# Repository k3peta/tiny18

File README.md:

# Tiny18

Tiny18 is a compact, 18-key wireless split keyboard designed for Japanese input. Each half uses a Seeed Studio XIAO nRF52840 and ZMK firmware.

日本語の説明は [`README.ja.md`](README.ja.md) を参照してください。

[Download the latest firmware](https://github.com/k3peta/zmk-config-tiny18/releases/latest) · [Firmware source](https://github.com/k3peta/zmk-config-tiny18) · [Keymap](https://github.com/k3peta/zmk-config-tiny18#default-keymap)

## Features

- 18 keys total (9 per half)
- Wireless split using Bluetooth Low Energy
- Seeed Studio XIAO nRF52840 controllers
- Kailh Choc (PG1350) switch footprints
- Diodeless, direct-pin wiring
- Reversible PCB: the same board is used for both halves
- Battery connector and hardware power switch on each half
- ZMK Studio support on the right/central half over USB

## Repository contents

This repository contains the production outputs for the PCB. The ZMK source and downloadable UF2 firmware are kept in the separate [zmk-config-tiny18](https://github.com/k3peta/zmk-config-tiny18) repository so that firmware builds remain small and reproducible.

| Path | Purpose |
| --- | --- |
| [`production/Tiny18mini.zip`](production/Tiny18mini.zip) | Gerber and drill files for PCB fabrication |
| [`production/bom.csv`](production/bom.csv) | Bill of materials exported from KiCad |
| [`production/positions.csv`](production/positions.csv) | Component placement data |
| [`production/designators.csv`](production/designators.csv) | Reference designator data |
| [`production/netlist.ipc`](production/netlist.ipc) | IPC-D-356 netlist for fabrication checks |

See [`production/README.md`](production/README.md) before ordering boards.

## Firmware

Prebuilt firmware is distributed from the [firmware Releases page](https://github.com/k3peta/zmk-config-tiny18/releases/latest). A release contains:

- `tiny18-right.uf2` — right half and Bluetooth central
- `tiny18-left.uf2` — left half and Bluetooth peripheral
- `settings-reset.uf2` — clears saved Bluetooth and split settings
- `SHA256SUMS` — checksums for the UF2 files

The right and left files are not interchangeable. Flashing the wrong file will not normally damage the controller; enter the bootloader again and flash the correct file.

### Flashing

1. Turn the keyboard's battery power switch off. Connect one half to the computer with a USB data cable.
2. Double-press the XIAO reset button. A drive named `XIAO-SENSE` should appear.
3. Copy the matching UF2 file to that drive:
   - right half: `tiny18-right.uf2`
   - left half: `tiny18-left.uf2`
4. Repeat for the other half, then disconnect USB and turn both halves on.
5. Pair the Bluetooth device named `tiny18` from the host computer.

For first-time setup, or when the halves no longer pair, flash `settings-reset.uf2` to both halves first. Enter the bootloader again, then flash the matching right and left firmware.

After clearing settings, remove the old `tiny18` entry from the host's Bluetooth settings before pairing again.

## Safety and scope

- Verify battery polarity before connecting a LiPo battery. Reversed polarity can damage the controller or battery.
- Turn battery power off while flashing over USB.
- These files are provided as-is. PCB fabrication, assembly, battery selection, and physical testing remain the builder's responsibility.
- The repository does not currently include a case or switch plate.

## License

The hardware production files in this repository are licensed under [CERN-OHL-P-2.0](LICENSE); see [`NOTICE`](NOTICE). Firmware is licensed separately under the MIT License in the firmware repository. Third-party components retain their own licenses.

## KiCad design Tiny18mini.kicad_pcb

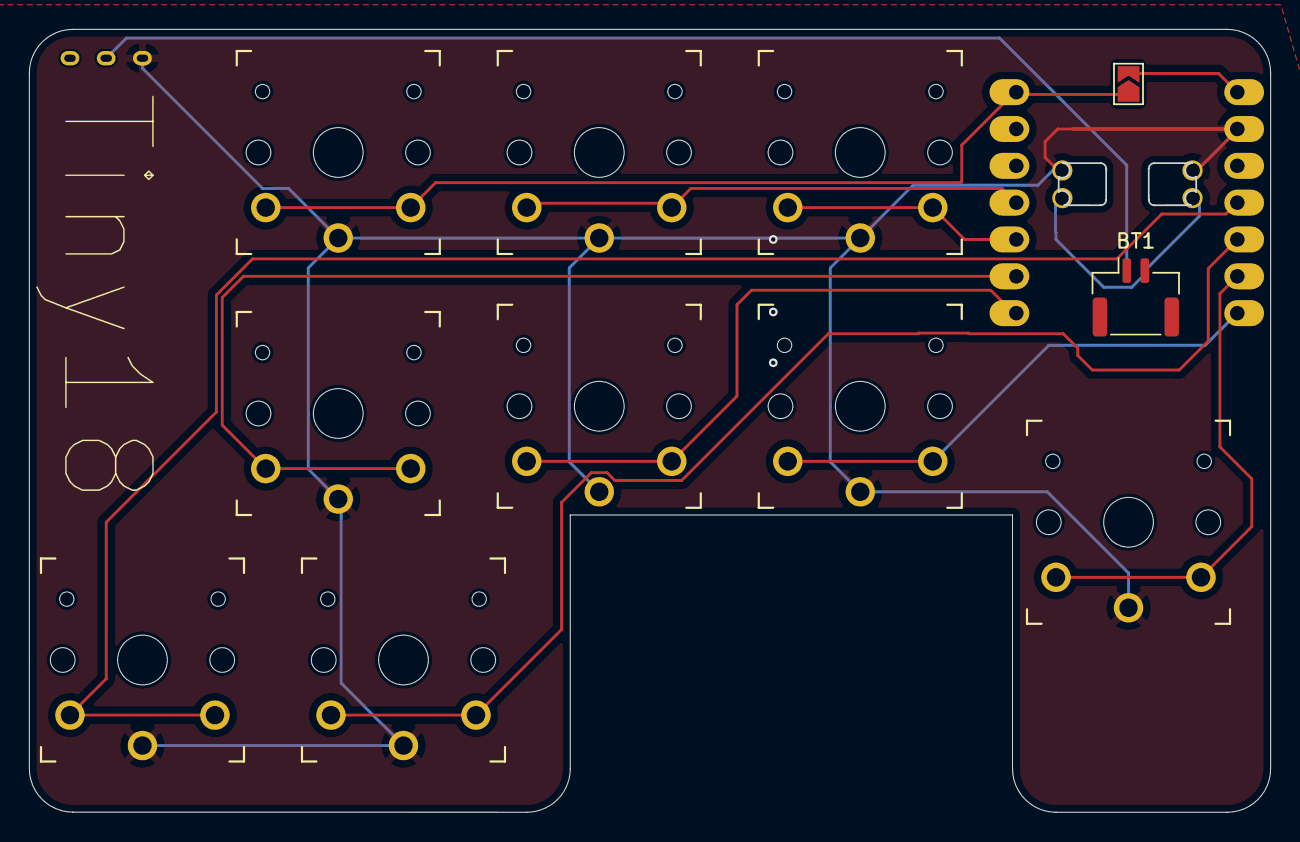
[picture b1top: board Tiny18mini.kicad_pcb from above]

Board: 2 copper layers, 85.5 x 53.9 mm, 13 parts (1 on the bottom side), 12 nets.

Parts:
BT1, BT1#2: Battery_Cell; JST_GH_SM02B-GHS-TB_1x02-1MP_P1.25mm_Horizontal
SW1, SW2, SW3, SW4, SW5, SW6, SW7, SW8, SW9: SW_Push; SW_PG1350_reversible
SW10: SW_SPDT; TGSW_MSK-12D19
U1: xiao-ble; XIAO_ble

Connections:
Bat: BT1.1 (+), BT1#2.1 (+), U1.19 (BAT)
D0: SW1.2, U1.1 (A2/0.02_H)
D1: SW2.2, U1.4 (A11/0.29)
D2: SW3.2, U1.5 (A8_SDA/0.04_H)
D3: SW4.2, U1.6 (A9_SCL/0.05_H)
D4: SW5.2, U1.7 (B8_TX/1.11)
D5: SW6.2, U1.8 (B9_RX/1.12)
D6: SW7.2, U1.9 (A7_SCK/1.13)
D7: SW8.2, U1.10 (A5_MISO/1.14)
D8: SW9.2, U1.11 (A6_MOSI/1.15)
GND: SW1.1, SW2.1, SW3.1, SW4.1, SW5.1, SW6.1, SW7.1, SW8.1, SW9.1, SW10.1 (A), U1.13 (GND), U1.20 (GND)
unnamed: BT1.2 (-), BT1#2.2 (-), SW10.2 (B)

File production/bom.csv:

Designator,Footprint,Quantity,Value,LCSC Part #
"BT1_2, BT1",JST_GH_SM02B-GHS-TB_1x02-1MP_P1.25mm_Horizontal,2,Battery_Cell,
"SW1, SW2, SW3, SW4, SW5, SW6, SW7, SW8, SW9",SW_PG1350_reversible,9,SW_Push,
SW10,TGSW_MSK-12D19,1,SW_SPDT,
U1,XIAO_ble,1,xiao-ble,
